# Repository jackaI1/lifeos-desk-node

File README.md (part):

# LifeOS Desk Node

I built a small desk display and room monitor because I wanted to see my next class at a glance and keep temperature and humidity readings in LifeOS.

The display is meant to show my next class or task beside the latest room
reading. LifeOS is my planning system. The device program wakes about every
five minutes, reads the sensor and sends readings over Wi-Fi to a small program
beside LifeOS, where they become daily room-log notes.

I can try the sensor queue and screen on my computer with the outage demo below.
It uses the same code as the device, with pretend readings and uploads. For the
physical display, I use the [parts and wiring](#parts-and-wiring) and
[build and flash](#build-and-flash) steps. I have software checks and a board
design; I still need to bench-test an assembled device, including its screen,
sensor accuracy and power draw.

## Try a sensor outage without a board

I use Guile, a program that runs Scheme, to turn a short scenario into sensor
bytes. A C program then feeds those bytes through the device's existing code.
Install Guile 3 with `brew install guile` on macOS or
`sudo apt-get install guile-3.0` on Ubuntu. With a C compiler and Make installed,
run these commands from the repository root:

```sh
make -C replay
guile --no-auto-compile -L replay/scheme replay/compile.scm < replay/examples/outage.scm > replay/build/outage.wire
replay/build/desk-replay --pbm replay/build/screen.pbm < replay/build/outage.wire
```

The example sends 70 good readings and one damaged reading before a simulated
upload. The result reports 64 uploaded, six dropped and one sensor fault. The
screen image is `replay/build/screen.pbm`, a plain black-and-white image file.
The [replay guide](docs/sensor-replay.md) explains how I change the readings,
repeat a sequence and view the image. These checks run the real sensor decoder,
queue and screen renderer, but the sensor and successful upload are simulated.

## Replay many scenarios at once

I built a parallel mode for the desk-node replay because I run a whole set of
sensor scenarios every time I change the firmware, and replaying them one after
another is slow. The replay now takes several scenario files and runs them on
several threads. A thread is a worker inside one program, so the workers can use
different processor cores at the same time. The program prints one summary line
per file, in the order I gave the files.

```sh
make -C replay
guile --no-auto-compile -L replay/scheme replay/compile.scm < replay/examples/outage.scm > replay/build/outage.wire
replay/build/desk-replay --jobs 4 replay/build/outage.wire replay/build/outage.wire
```

Each line is the same summary the single-file mode prints. `--jobs 1` runs
everything on one thread, and the output is byte-for-byte the same for any number
of threads. The tests run 240 jobs at 2 to 64 threads and compare every byte.
If one file is bad, the program prints the first bad file's name and reason to the
error output, prints nothing else, and exits with an error.

The main thread reads each file into one of eight slots in a block of shared
memory. Workers take the next file in order, replay it, and keep their results in
their own lists. At the end the results are put back in file order and printed.
One mutex, which is a lock, and two condition variables, which let a thread wait
for a signal, keep two threads from touching the same slot at once.

On my Mac, 2000 copies of a 4,095-sample scenario took 0.17 seconds on one thread,
0.08 seconds on two and 0.04 seconds on four. Past four threads, the main thread's
file reading is the likely limit. The parallel mode prints only the summaries. The
screen image (`--pbm`) and UART log (`--uart-log`) still need the single-file
mode, and each file must be under 64 KiB.

CI builds the replay with ThreadSanitizer, which reports threads that touch
shared memory without a lock, and with AddressSanitizer, which reports bad memory
access. Both run in the sensor replay job on Linux and macOS. The locking rules,
the shared memory block and the reasons for each choice are in the
[threading design](docs/parallel-replay.md).

## Check a wire recording without a board

I use sigrok, a tool that reads logic-analyzer recordings, to decode the sensor
messages and serial output. On macOS, install `brew install sigrok-cli guile`;
on Ubuntu, use `sudo apt-get install sigrok-cli guile-3.0 build-essential`.
With Python 3.11 or newer, Make and a C compiler, run from the repository root:

```sh
python3 -m venv .venv
.venv/bin/python -m capture.demo
.venv/bin/python -m capture.decode replay/build/captures/clean.sr
```

The demo generates clean and deliberately damaged recordings from the same sensor
scenarios and serial-log code used by the replay. Each clean recording gives one
25 C / 50% reading and 83 serial bytes with no findings. Each damaged recording
reports a rejected address, a missing acknowledgement clock, a bad sensor checksum,
an unfinished message and a serial framing error, meaning a missing stop bit.
The recordings and readable JSON reports are in `replay/build/captures/`.

For a real recording, run `.venv/bin/python -m capture.decode wake.sr --report report.json`.
The tool accepts sigrok `.sr` sessions and uniformly sampled CSV exports. The
[capture guide](docs/capture-decoding.md) covers recording pins, channel names,
sample rates, changing scenarios and reading fault locations. Generated captures
are synthetic; they do not establish that an assembled board works.

## Try the room-control demo

From the repository root, with Python 3.11 or newer:

```sh
python3 -m venv .venv
.venv/bin/python -m pip install -r automation/requirements.txt
.venv/bin/python -m automation.gateway --demo
```

Leave that running and open another terminal in the same folder:

```sh
.venv/bin/python -m automation.check
```

The check prints the room readings, asks for heat, then lowers the target and
checks that heat and fan turn off. It restores the previous settings when done.
Press Ctrl-C in the first terminal to stop the demo and release its connections.
The outputs are simulated; they do not switch a heater or fan in my room.

Modbus TCP and BACnet/IP are two network protocols, or sets of rules for exchanging
readings and commands. This demo exposes the same readings and thermostat through
both. The [building-control guide](docs/building-automation.md) explains the point
addresses, how to connect the existing desk-node readings, and how these protocols
fit into heating, ventilation, air conditioning and electrical systems.

## Check noisy room readings

I use a moving median, the middle reading in a small sliding group, to remove
isolated spikes. A low-pass filter then keeps slow changes and reduces faster
ones. An FFT, a calculation that separates repeating changes by frequency, helps
me find interference that repeats at a regular interval.

The demo above makes a week's worth of five-minute readings with a known room
temperature, a faster unwanted cycle, random noise and occasional spikes. With
the default seed, the typical error falls from 0.5232 C to 0.1109 C after
filtering. The [short comparison report](docs/signal-analysis-report.md) includes
the raw and filtered errors and the detected noise frequencies. These are
software results against a simulator, not measurements of the physical sensor.

For a real adapter database, I choose one device and analyze a continuous stretch
of readings. The database opens read-only; the report goes into a new folder:

```sh
.venv/bin/python -m analysis --database room.sqlite3 --device desk-1 \
  --channel temperature --cutoff-hz 0.000277777778 --output analysis/build/room
```

This example keeps changes slower than roughly an hour and removes faster ones.
The [guide](docs/signal-analysis.md) covers choosing that boundary, humidity and
CSV input, missing readings, the estimated noise ratio and the filter's limits.
The filters run after collection; they do not change live readings or thermostat
commands. Five-minute logs cannot identify rapid electrical noise such as mains
hum, and smoothing can remove a real rapid change too.

## Rehearse a controller or connection fault

I can check the sensor's Bluetooth packet, Wi-Fi retry decisions and damaged
GPS or vehicle-data recordings on my computer. I can also run the C++ sensor
program on an emulated STM32 and follow a deliberately triggered processor
fault back to its instruction. The [embedded guide](docs/embedded-lab.md)
explains the commands, what each check means and what is simulated.

For a longer control experiment, my [controller rehearsal](robot_controller/)
records timing and sensor data while a simulated heater and two-joint arm run.
Its saved readings feed the same controller-message decoder above. The
[connection rehearsal](network_lab/) tries two delayed or interrupted upload
links and a radio waveform with a simulated frequency shift. Both run without
physical machinery or a paid cloud account.

I also keep a [water-probe board](hardware/leak/) and a
[light-input circuit calculation](hardware/simulation/report.md) here while I
learn how to extend the node. They include circuit checks and simulation plots;
neither circuit has been manufactured. The [Linux sensor experiment](linux_sensor/)
puts the same checked sensor bytes behind a device file inside an emulated ARM
computer. The [concurrent receiver](tcp_telemetry/) and
[port-switch service](optical_switch/) are separate local networking experiments.

## Plan the board and connections

I can compare the original USB board with a smaller battery design before
ordering either one. From this folder, with Python 3.11 or newer, run:

```sh
python3 -m power_budget.compare
```

It shows where current goes and estimates battery life. With the documented
example assumptions, calculated average input current falls from 11.960 mA to
6.715 mA. These are datasheet calculations, not measurements. The new
[48 × 54 mm battery board](hardware/revb/README.md) has a charger and a regulator
that uses less current itself. I still need to build it and fill in the
[bench measurement sheet](docs/power-and-battery.md#bench-sheet-intentionally-empty).
I also have an [antenna matching calculator](docs/antenna-matching.md) that reads
radio measurements and suggests small components to reduce reflections. Its
included example uses clearly labelled synthetic data; I have not measured an antenna.

I use a wiring plan for removable sensor and programming leads so I can cut
and label each wire and check it before powering the board. With Python 3.11 or
newer, I can make the documents without a board or extra packages:

```sh
python3 -m harness.check harness/example.json
python3 -m harness.generate harness/example.json --output harness/build
```

Open `harness/build/harness.svg` for the drawing and the CSV files for the cut
list, labels and continuity and polarity test sheet. The example covers the J2
sensor expansion and J3 programming header. The [harness guide](docs/harness.md)
explains how to change lengths and pin assignments and check the real wiring.

I also keep a purchasing record for the board so I can check replacements and
missing material declarations before ordering parts. It covers all 31 components,
with nine replacement candidates and a spreadsheet for an assembler. With
Python 3.11+, KiCad 8 and its command-line tools installed, I can try it without
a board or an account:

```sh
python3 -m venv .venv
.venv/bin/python -m pip install -r hardware/components/requirements.txt
.venv/bin/python -m hardware.components --boards 10
```

Open `hardware/build/components/desk-node-cm.xlsx`, or download the
[example spreadsheet](hardware/components/review/desk-node-cm.xlsx). The
[parts guide](docs/components.md) shows how I load the same records into InvenTree,
a free parts manager, and explains the risk report. RoHS and REACH are rules about
restricted substances; missing manufacturer evidence stays marked unverified.
The replacement parts are candidates that still need board testing.

I can also check whether sudden jumps in the room log are likely to be noise.
The analysis tool smooths isolated spikes and faster variations, then shows which
repeating changes remain. To try it without a board, with Python 3.11 or newer,
run from this folder:

```sh
python3 -m venv .venv
.venv/bin/python -m pip install -r analysis/requirements.txt
.venv/bin/python -m analysis.demo
```

Open `analysis/build/demo/report.md` for the comparison against known true
readings. The [analysis guide](docs/signal-analysis.md) shows how I use the same
filters on my saved room logs. All demo readings are generated on the computer.

I can also rehearse damaged controller messages before connecting a controller.
The recording tool turns bytes into temperatures and heater/fan commands, reports
missing or damaged messages and turns simulated outputs off when a check fails.
CAN is a wired message network; its FD variant carries longer messages. To try it:

```sh
python3 -m venv .venv
.venv/bin/pip install -r can_monitor/requirements.txt
.venv/bin/python -m can_monitor.replay --generate /tmp/desk-can.jsonl --faults
.venv/bin/python -m can_monitor.replay /tmp/desk-can.jsonl --tail 3
```

The [controller recording guide](docs/can-control.md) explains the errors,
message rates and Linux virtual network. These are simulated messages, including
a 64-byte CAN FD snapshot. My current desk board has no CAN transceiver.

For missing room logs, I can separately test delayed or lost network replies and
save sensor batches through an encrypted message broker. The
[connection guide](docs/network-monitoring.md) gives the demo commands, network
layout and alarm rules. The [charging model](power_budget/charging.py) adds a
calculated charge-time estimate to the existing battery budget.

## Parts and wiring

The controller is an ESP32-WROOM-32E, a small computer with Wi-Fi and 4 MB of
program storage. I use an OLED, a compact light-emitting screen, for the display.
SPI and I²C are the wired connections to the screen and sensor; UART is the
serial connection used to load the program and read logs. The firmware needs:

- An SHT31 temperature/humidity sensor at address `0x44`.
- An SSD1306 128 by 64 OLED module with a seven-pin, four-wire SPI connection.
- A regulated 3.3 V supply for the controller and peripherals, from USB desk power.
- A 3.3 V USB-to-UART adapter for flashing and reading the serial log.

The [wiring guide](docs/pinout.md) gives the exact pins, power requirements and
pull-up resistors. A four-pin I²C OLED is a different variant; select the legacy
display option explicitly if using that wiring. Do not connect both displays.
The OLED stays powered while the ESP32 sleeps. Rev A uses USB desk power;
Rev B adds a battery option while retaining that display behavior. Neither has
a measured battery-life claim.

## Circuit board

I designed the [board](hardware/) to hold the controller, temperature and humidity
sensor, and USB-C power supply. The screen plugs into it. A separate USB-to-UART
adapter loads the firmware and lets me read its logs. The
[board guide](hardware/README.md) explains the connections, parts and files needed to order or build one. This version has not been manufactured yet.

## Check the power-up on a bench

I built a bench check because I need the same power-up measurements every time I change the board, and I want them written down. The script drives a programmable power supply and an oscilloscope. It sets the 5 V input, turns it on, and records the ripple on the 3.3 V regulator's output (the small repeating wiggle on a supply line) and how long after the 5 V input that output comes up. It also reads how much current the board draws. Each result is compared with a limit in a text file, and each run is saved in a folder named with the time it ran.

I don't have the lab instruments here, so the check runs against simulated ones. It sends SCPI, the standard text commands most bench supplies and scopes use, through PyVISA, a Python library that talks to instruments. A second library, pyvisa-sim, answers those commands from a file that describes a simple board. To run it:

```sh
python3 -m venv .venv
.venv/bin/python -m pip install -r bench/requirements.txt
.venv/bin/python -m bench
.venv/bin/python -m bench --inject ripple
```

The first run passes all five checks: 8 mVpp of ripple (limit 30), a 1.5 ms delay for the regulator (limit 0.2 to 10 ms) and 60 mA of input current (limit 150 mA). The `--inject` option adds a fault to the simulated board. `ripple` adds 60 mVpp, and `late-rail` starts the regulator 14 ms late. Each fault fails the check it targets and nothing else, and the tests check that. Each run writes a CSV of measurements, a CSV of the captured waveforms and a short report into `bench/build/runs/`. The limits in `bench/limits.toml` are bring-up targets I picked, not datasheet numbers. The [bench guide](docs/bench-automation.md) covers the commands, how the simulator models the board and how to point the script at real instruments.

## Export the light-input circuit for OrCAD

I built an OrCAD export because I wanted to learn Cadence OrCAD, a circuit
design and simulation program that many electronics teams use. My light-input
circuit is in KiCad, so I wrote a script that turns it into an OrCAD PSpice
netlist. A netlist is a plain text file that lists each part and the points it
connects to. The script takes the feedback resistor and capacitor values from the
KiCad drawing, so the netlist cannot drift from the drawing. It also refuses to
write a netlist if those two parts are not wired to the amplifier's output and
input pins.

To check the file, the script runs it in ngspice, a free simulator that runs on
my Mac. It runs DC, frequency and time-step analyses from the same file and
compares the results with my hand calculations.

```sh
python3 -m hardware.simulation.orcad --out hardware/simulation/build/orcad
```

This needs `kicad-cli` and `ngspice` installed. It writes `light-front-end.cir`,
the OrCAD netlist, and `check.json`, the measured results. On my last local run
the gain was 99,999 ohms, the bandwidth was 16.8 kHz against a hand value of
15.9 kHz, and the step settled at 1.74998 V. The [circuit report](hardware/simulation/report.md)
explains what the model leaves out. OrCAD is a desktop program, and I have not
opened this netlist in it yet, so the checks I have are the ngspice run and the
tests in `hardware/simulation/tests/test_orcad.py`.

Syntax note: the two behavioral sources (the supply reference and the output
clamp) are written as PSpice `VALUE {...}` cards, not the `V=` form that ngspice
accepts on its own. PSpice does not read `V=`, so I changed them. The tests check
the card shapes, but no PSpice program has read the file yet, so importing it into
OrCAD is still the next step.

## Build and flash

Install [ESP-IDF v5.4.2](https://docs.espressif.com/projects/esp-idf/en/v5.4.2/esp32/get-started/index.html)
with its ESP32 toolchain, the tools for building and loading the device program.
In an activated ESP-IDF shell, from this checkout:

```sh
cd firmware
idf.py set-target esp32
idf.py menuconfig
idf.py build
idf.py -p /dev/cu.YOUR_USB_UART flash monitor
```

In menuconfig, open LifeOS Desk Node and choose the display, Wi-Fi settings,
service address and device token. Replace the example serial port with the adapter's
port. The [firmware guide](firmware/README.md#build-and-flash) covers programming
mode, serial logging and configuration. Configured binaries contain the Wi-Fi
credentials and token; keep them and `sdkconfig` private.

## Connecting it to LifeOS

The ESP32 talks to the included [API adapter](firmware/tools/desk_api.py), a
small service that translates requests between the device and LifeOS. An API
is the set of requests programs use to communicate. The adapter needs Python
3.9 or newer and stores readings in SQLite, a database kept in a local file.
Follow the
[adapter setup](firmware/README.md#lifeos-api-adapter) to create a private device
token, try the isolated demo and then configure a real LifeOS connection.

Demo mode uses fictional events and never contacts LifeOS. Its default address,
`127.0.0.1:8091`, is for trying it on the computer. For the desk device, use a
network-reachable address and the HTTPS setup in the guide. HTTPS encrypts
the connection and checks the server's identity. Keep LifeOS account
credentials on the computer, not on the microcontroller.

The adapter picks the earliest upcoming school event or task deadline visible
through LifeOS. A date-only deadline says that its time is unknown. Readings go
into new daily notes named `Desk room <day> <device>`. Retries do not duplicate
readings, and edits to a managed note's text stop syncing rather than overwrite
the edit.

## When the connection is down

The screen keeps the last fetched event and marks it offline, so it can be stale.
Up to 64 readings wait for upload across sleep cycles. If that fills, the oldest
reading is dropped and the screen shows a loss count. Turning the power off loses
those pending readings; they are not saved to flash. Invalid sensor readings
are not turned into made-up values.

## Read the room sensor from my phone

I added Bluetooth Low Energy to the desk node because I wanted to read the room temperature and humidity from my phone without needing Wi-Fi. Bluetooth Low Energy is a short-range radio that uses very little power. The desk node now advertises as `Desk room sensor`, so my phone can find it, connect and read the latest values. The default build leaves Bluetooth out, so existing builds work as before.

After each wake, the node takes its usual reading, uploads it over Wi-Fi as before, and then keeps Bluetooth on for a short window, 30 seconds by default. While a phone is connected, the node reads the sensor again every 10 seconds. It sends a notification only when the temperature has moved by 0.1 °C or the humidity by 0.5 %, and never more than one every 10 seconds. When the window ends, the radio shuts off until the next wake.

The values use the standard Environmental Sensing service from the Bluetooth standards group, so any generic Bluetooth app can read them. The firmware uses NimBLE, the small Bluetooth stack that ships with ESP-IDF, the official ESP32 software kit. Temperature is a signed 16-bit number in hundredths of a degree (characteristic `0x2A6E`). Humidity is an unsigned 16-bit number in hundredths of a percent (`0x2A6F`). The encoding and the notification rule are plain C in [`firmware/components/desk_ess`](firmware/components/desk_ess/). The host tests in [`firmware/tests/test_ess.c`](firmware/tests/test_ess.c) run them under AddressSanitizer and UBSan, with out-of-range values and bad checksums included: 37 checks.

How to try it:

1. Build the Bluetooth version with `idf.py -D SDKCONFIG_DEFAULTS="sdkconfig.defaults;sdkconfig.ble.defaults" set-target esp32`, then `idf.py build` and flash it.
2. On a phone, open nRF Connect (a free Bluetooth scanner app), scan, and tap `Desk room sensor` within 30 seconds of a wake. The node wakes every 5 minutes by default.
3. Read the temperature characteristic (`0x2A6E`). It shows two bytes such as `59 08`. Decode them with `python3 firmware/tools/ess_decode.py temperature "59 08"`, which prints `21.37 degC`.

The phone only sees the node during the window after each wake. It is not a live stream. A shorter sleep interval gives more windows but uses more power. I have not run this on a real board yet. CI builds the Bluetooth version next to the default one, and runs the encoder tests on every push. The [firmware README](firmware/README.md#bluetooth-low-energy-optional-build) has the build details.

## Send readings over a wired CAN link

I built a wired CAN link for the desk node because Wi-Fi drops, and when it does I lose the room readings until it comes back. CAN is a wired message bus: devices share two wires, and each short message reaches every device on the bus. The node sends its latest temperature, humidity and fault flags once per wake cycle, using the ESP32's built-in CAN controller. A second device on the bus, or my laptop with a recording, can read them later.

The analyzer reads a recorded CAN log and flags what I care about: a gap in the heartbeat (the regular message that shows the node is alive), values outside the range the message layout allows, the node's own sensor and queue fault flags, and bus-off, when the controller stops sending because too many of its messages failed. It runs on a computer with no board attached:

```sh
python3 -m venv .venv
.venv/bin/python -m pip install -r can_monitor/requirements.txt
.venv/bin/python -m can_monitor.analyze can_monitor/examples/candump/desk_node_clean.log
.venv/bin/python -m can_monitor.analyze can_monitor/examples/candump/desk_node_faults.log
```

The clean log passes. The second file is the same log with damage I added on purpose: 10 readings missing, a humidity of 105 %, a sensor fault, a bus-off event, a damaged line and a time that goes backwards. The analyzer reports each one and exits with status 1. Both logs come from a simulated node on a virtual bus, not from a real board. The [CAN guide](docs/can-log-analysis.md) lists every finding, the byte layout and the firmware switch (`CONFIG_DESK_CAN_ENABLE`). The desk board has no CAN transceiver yet, so the link has not run on a real bus. CI builds the firmware with the CAN link enabled, runs the C encoder tests, and checks the same bytes against the message file in Python.

## Check the case before printing

I built a set of simulations for the case because I wanted to know whether it fits the board and survives being knocked before I print it. The scripts in [mechanical/](mechanical/README.md) draw the case from its dimensions, load it on a computer the way a lid screw or a drop would, and report the peak stress, how far it bends and its safety factor against yielding. A second script adds up the size errors of the board, the standoffs and the printed case to check the screw fit.

The first run found one thing to change: with the 3.2 mm mounting holes on my board, an M3 screw misses the worst-case fit by 0.115 mm, and a 3.5 mm hole passes. The numbers are in [mechanical/docs/study.md](mechanical/docs/study.md), and the setup steps are in the [mechanical README](mechanical/README.md). The checks run in GitHub Actions on every change to that folder.

## Check my room readings for odd values

I built a small anomaly check for the temperature and humidity readings because I want the desk node to notice a sensor spike or a stuck value itself, before it reaches my room log. A small neural network learns what a normal reading looks like from a log, and a window of four readings gets a high score when it looks wrong. I shrank the model to eight-bit integers, so it could run on the ESP32 later. The C code uses only integer arithmetic.

On a simulated log with known faults, the eight-bit model gets the same accuracy as the full-precision model (0.968 on the held-out part), agrees with it on 99.56 % of windows, and uses 223 bytes for its weights instead of 592. It catches spikes, humidity jumps and dropouts every time. It misses stuck readings, because four identical values look like a calm room. The [anomaly README](anomaly_int8/README.md) has the numbers and the per-layer scales, and [anomaly_int8/docs/results.md](anomaly_int8/docs/results.md) has the full report. To run it:

```sh
cd anomaly_int8 && python3 -m venv .venv && . .venv/bin/activate
python -m pip install --index-url https://download.pytorch.org/whl/cpu torch==2.9.1 && python -m pip install -r requirements.txt
python -m pytest && python -m anomaly_int8 run
```

## Check the sensor checksum in hardware

The sensor sends a checksum with each reading, and the firmware throws away readings whose checksum does not match. I wrote the same check as logic blocks in Verilog, the language that describes chips and FPGAs, because a hardware version is one option for the sensor path later. The blocks are tested in simulation against the same scenario files the firmware tests use, including the ones with deliberately corrupted checksums. The [rtl README](rtl/README.md) explains each block.

The word checker agrees with the replay tool on all 2,204 words I tested, and the reading buffer's built-in self-test finds all 512 memory stuck-at faults I injected, and all 22 scan-chain faults. The sensor path also maps onto 588 LUT4 cells and 440 flip-flops in Yosys for an iCE40 FPGA.

```sh
cd rtl && python3 -m venv .venv && . .venv/bin/activate && python -m pip install -r requirements.txt
make test PY=python3     # lint, cocotb frame tests, Verilator benches, cross-checks
make synth               # FPGA-style synthesis and logic depth
```

## Place and route the sensor block

I ran the sensor block through OpenROAD, an open-source chip design flow, to check that it can run at the speeds I would need for a chip or an FPGA version of the sensor path. The flow does synthesis, placement and routing on the open Nangate45 cell library. I swept the clock period and the core utilization and recorded the timing slack, area and power for each run. Every run meets timing, the tightest at 1.2 ns with 0.080 ns to spare, and CI fails if the chosen 1.2 ns constraint ever stops closing. The table and the commands are in [rtl/README.md](rtl/README.md) and [rtl/docs/openroad-sweep.md](rtl/docs/openroad-sweep.md).

## Run the sensor check on an FPGA board

I wanted the sensor checksum logic to run on a real FPGA, a chip you can reprogram, and not only in a simulator. The sensor check in `rtl/` is written in Verilog, so I added a board version of it for the iCEBreaker, a small board with an iCE40 UltraPlus FPGA, a 12 MHz clock and a USB serial port. Its FPGA is one of the open-source chip families, so I can build the program for it with free tools.

The computer sends sensor bytes over the USB serial port. Each transfer starts with a length byte, then the bytes. The board checks each six-byte frame in the same hardware block as before, keeps the good ones and sends back six bytes with the good, bad and cut-short counts. The green LED is on while a transfer is arriving. The red LED comes on after any bad or cut-short frame.

```sh
cd rtl && python3 -m venv .venv && . .venv/bin/activate && python -m pip install pyserial
python3 board/icebreaker/host.py --port /dev/tty.usbserial-XXXX --demo
```

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
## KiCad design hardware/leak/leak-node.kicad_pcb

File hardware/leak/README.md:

# A water-probe board for my desk node

I built a small water-probe interface because I wanted to learn how to add a
simple leak indication beside the desk node's room readings. Two external probe
contacts act like a resistance: water lowers it, the board turns on a red light
and its output changes for a microcontroller to read. This is an unmanufactured
prototype, not a dependable flood alarm.

`leak-node.kicad_sch` is the circuit drawing and `leak-node.kicad_pcb` is its
45 by 35 mm, two-copper-layer layout. The exact footprints are kept in `Leak.pretty` and embedded in the board;
`bom.csv` records values, footprints and manufacturer part numbers. The MCU header is J1:
1=3.3 V, 2=ground, 3=active-low alert, 4=probe voltage for an ADC. J2 connects
the two external conductive probe contacts. The board does not include an MCU.

With KiCad 8 command-line tools installed, from the repository root:

```sh
hardware/leak/check.sh
```

I get electrical-rule and layout-rule reports, a PDF circuit drawing, a bill of
materials with manufacturer part numbers, and Gerber/drill files for fabrication
in `hardware/leak/build`. CI fails for any reported rule violation, including
schematic/layout disagreement, and saves those files as downloadable artifacts.
The check does not open a desktop application. Source changes can be regenerated
with `scripts/generate.py`; `scripts/board.py` does headless placement and imports
batch routes. The committed board is already routed and needs no router to check.

## Why these parts and dimensions

A 1 megohm pull-up keeps dry-probe current low. An LMV331 comparator compares the
probe voltage with half the supply from two 100 kilohm resistors. Its output
sinks current for the LED and has a separate 10 kilohm pull-up for the MCU. A
10 megohm feedback resistor gives hysteresis, so the output does not keep
switching at exactly one resistance. The ideal wet threshold is about 909
kilohms and release threshold about 1.11 megohms; real leakage, comparator offset,
probe contamination and water composition can move them. I must measure this
before choosing a useful physical threshold.

The 100 nF capacitor is beside the comparator supply. I use 0.25 mm signal
tracks, 0.20 mm net clearance, 0.6 mm vias with 0.3 mm drills and at least
0.3 mm copper-to-edge clearance. The current is low, so these widths are chosen
for routing and fabrication margin, not a high-current power path. The high
resistance input makes clean PCB surfaces, short probe leads and protection
against electrostatic discharge important. Continuous DC can corrode a wet
probe; intermittent power and a corrosion study are future hardware work.
The [simulation report](../simulation/report.md) shows the ideal threshold sweep
and the separate light-sensor amplifier calculation. No actual leakage, battery
draw or water response has been measured.

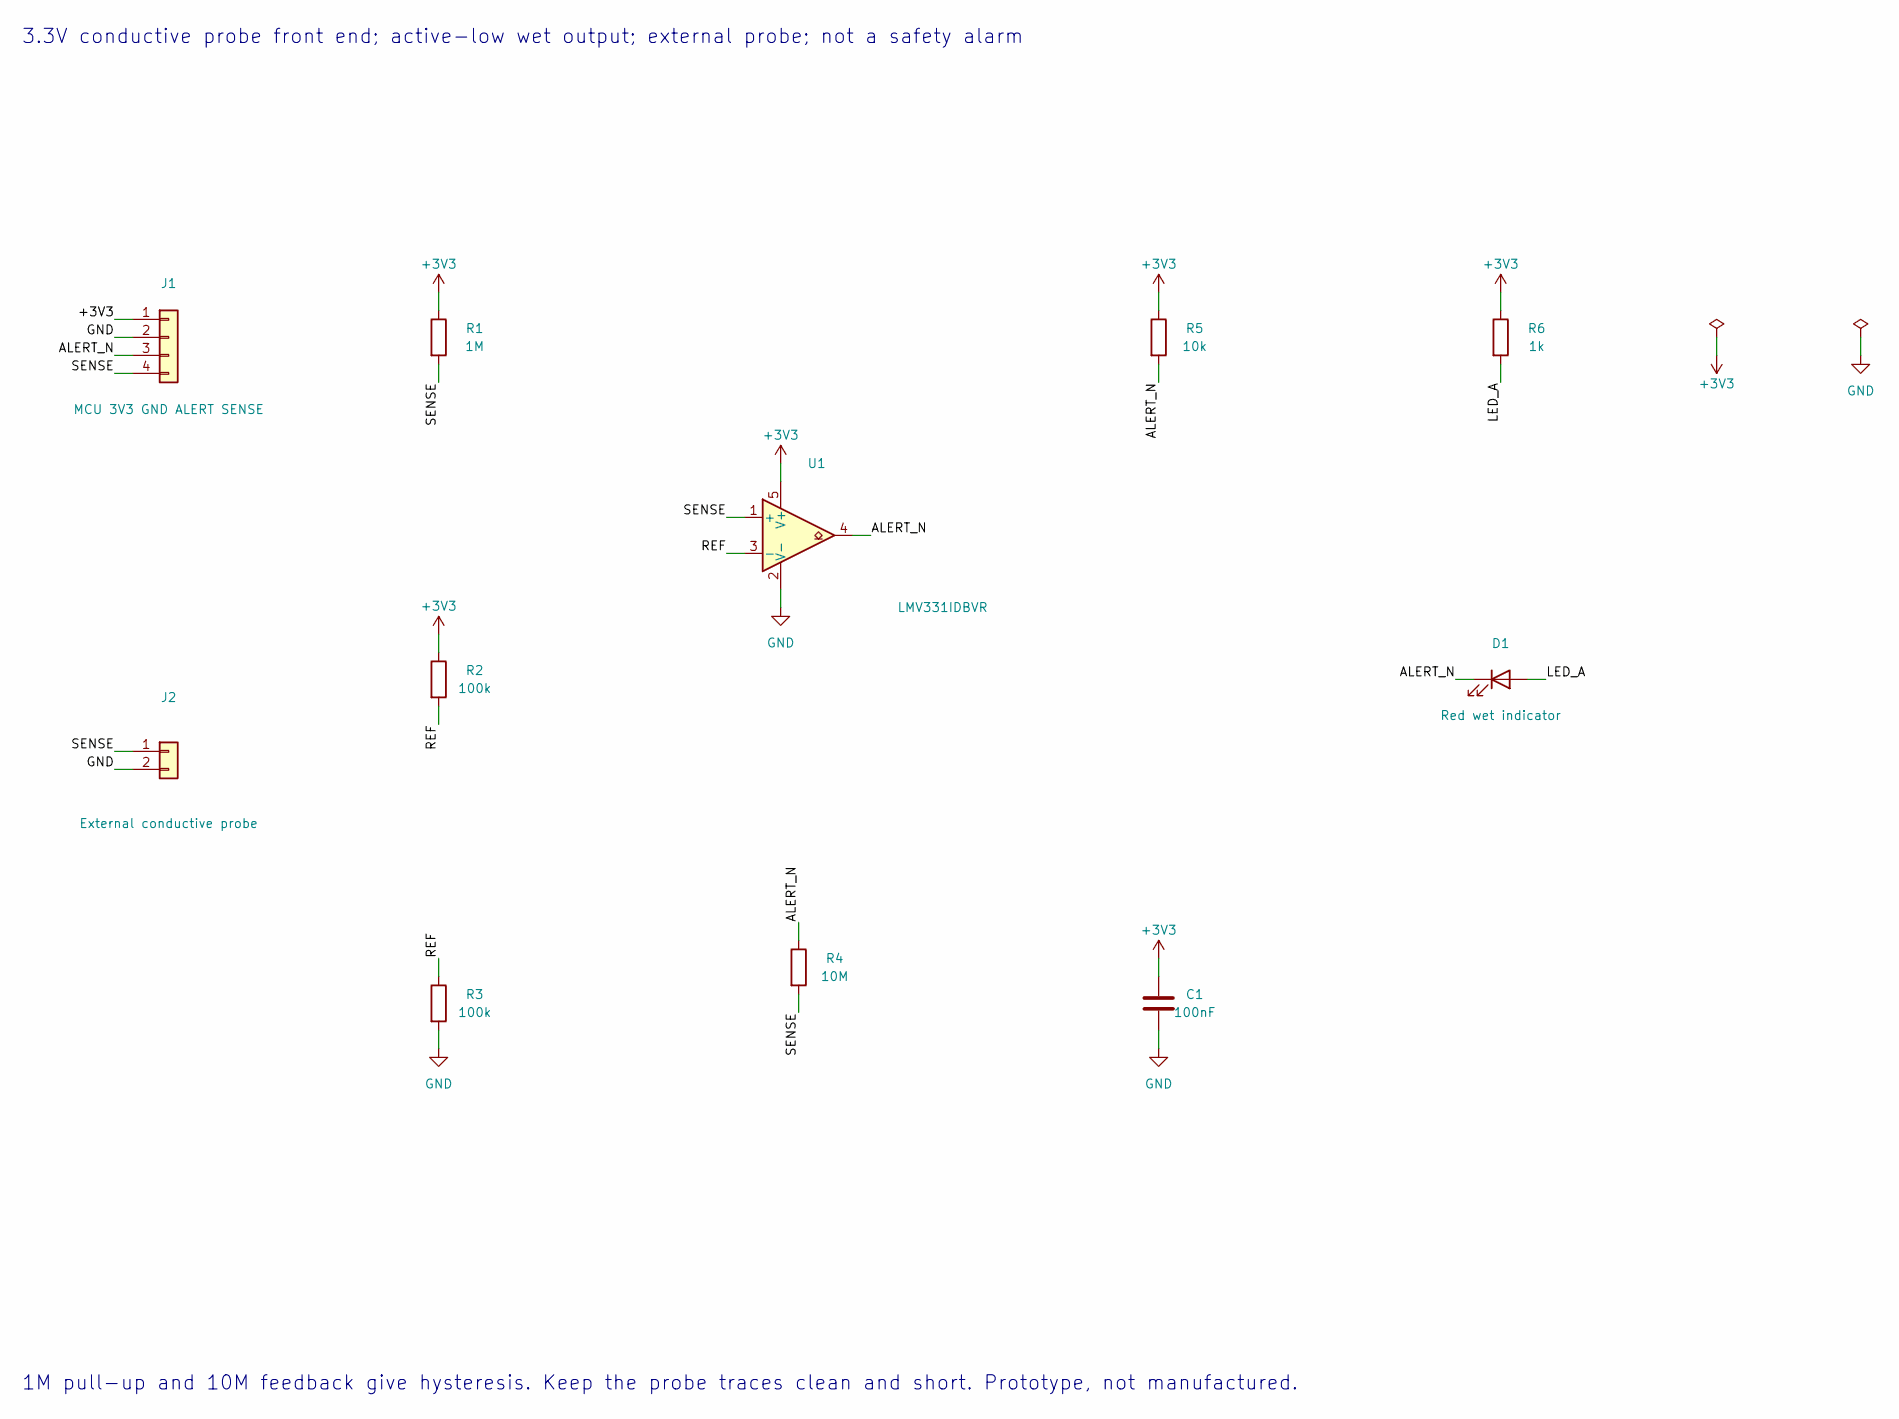
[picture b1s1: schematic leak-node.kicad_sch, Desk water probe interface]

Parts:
C1: 100nF; C_0603_1608Metric; MPN GRM188R71C104KA01D
D1: Red wet indicator; LED_0603_1608Metric; MPN LTST-C190KRKT
J1: MCU 3V3 GND ALERT SENSE; PinHeader_1x04_P2.54mm_Vertical; MPN Samtec TSW-104-07-G-S
J2: External conductive probe; PinHeader_1x02_P2.54mm_Vertical; MPN Samtec TSW-102-07-G-S
R1: 1M; R_0603_1608Metric; MPN RC0603FR-071ML
R2, R3: 100k; R_0603_1608Metric; MPN RC0603FR-07100KL
R4: 10M; R_0603_1608Metric; MPN RC0603FR-0710ML
R5: 10k; R_0603_1608Metric; MPN RC0603FR-0710KL
R6: 1k; R_0603_1608Metric; MPN RC0603FR-071KL
U1: LMV331IDBVR; SOT-23-5; MPN LMV331IDBVR

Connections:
+3V3: C1.1, J1.1, R1.1, R2.1, R5.1, R6.1, U1.5 (V+)
/ALERT_N: D1.1 (K), J1.3, R4.1, R5.2, U1.4
/LED_A: D1.2 (A), R6.2
/REF: R2.2, R3.1, U1.3 (-)
/SENSE: J1.4, J2.1, R1.2, R4.2, U1.1 (+)
GND: C1.2, J1.2, J2.2, R3.2, U1.2 (V-)

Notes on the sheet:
3.3V conductive probe front end; active-low wet output; external probe; not a safety alarm
1M pull-up and 10M feedback give hysteresis. Keep the probe traces clean and short. Prototype, not manufactured.

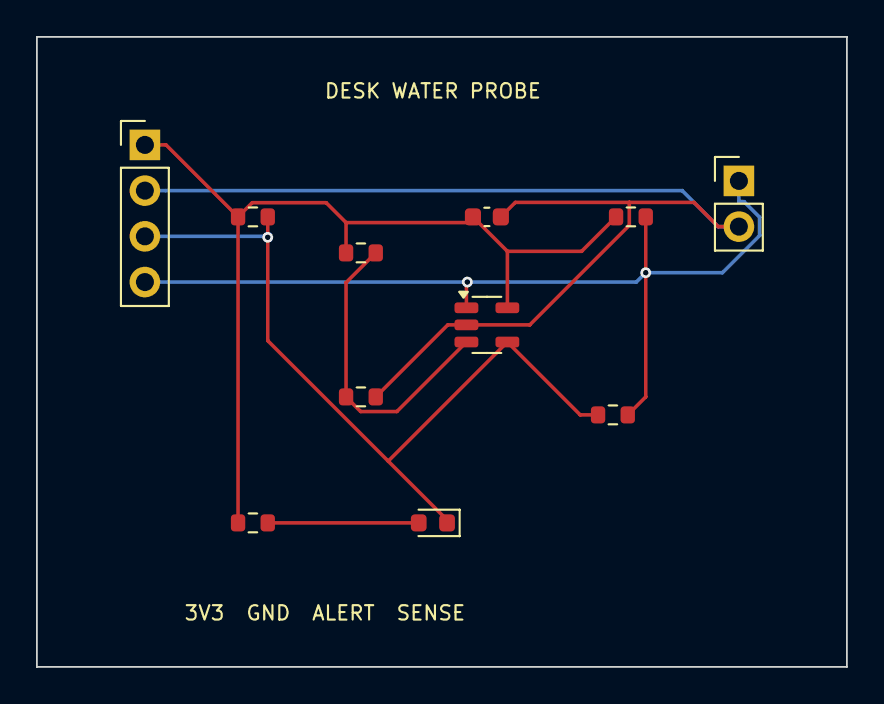
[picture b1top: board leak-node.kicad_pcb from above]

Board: 2 copper layers, 45.0 x 35.0 mm, 11 parts (0 on the bottom side), 6 nets.

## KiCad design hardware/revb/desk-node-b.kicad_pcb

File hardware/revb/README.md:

# Battery desk node, Rev B

I built a smaller battery board because the USB version's regulator and power
light keep drawing current between updates. This version keeps the working
firmware pin assignments and the screen's last image, adds a LiPo charger, and
uses a regulator with a much smaller standing current. It is a routed prototype
design, not an assembled or measured board.

Open [desk-node-b.kicad_pro](desk-node-b.kicad_pro) in KiCad 8 to inspect the
circuit drawing and physical board. With KiCad 8 and Python 3.11 or newer on PATH:

```sh
hardware/revb/check.sh
python3 -m power_budget.compare
```

The first command checks the circuit and copper, checks the firmware pins and
battery connections independently, then exports files into `hardware/revb/fab/`.
The second prints calculated current and runtime. The
[power guide](../../docs/power-and-battery.md) explains every input and has an
empty table for real microamp-meter measurements.

## What changed

| Design choice | Rev A | Rev B |
| --- | --- | --- |
| Board bounding size | 50 × 55 mm | 48 × 54 mm, 5.75% less area |
| Supply | 5 V USB | Protected 1S LiPo, 4.2 V full; USB charges only |
| Regulator | AZ1117C-3.3, 4 mA typical own current | AP2112K-3.3, 55 µA typical own current, 600 mA output rating |
| Always-on light | Red LED through 1 kΩ | Removed |
| Charger | None | MCP73831T-2ACI/OT, 4.2 V, 100 mA set by 10 kΩ |
| Display | Powered throughout sleep | Same, no firmware changes |
| Signal connectors | J2 I²C, J3 UART, J4 SPI | Same pin assignments |

Dimensions describe the **carrier PCB**, not the complete assembled envelope:
the module antenna overhangs the top edge by 6.19 mm and connectors extend beyond
the board. The battery and display are external. The top slot ends at x = 46.5 mm;
the SHT31 sensor remains on the slotted peninsula. Antenna copper exclusions,
0.3 mm minimum drill, two copper layers and 0.15 mm minimum track/space are kept.
The module uses its factory antenna and match; the
[RF calculator](../../docs/antenna-matching.md) is for a future external feed,
not for attaching parts to the carrier's digital pins.

## Battery and charging connections

Use one protected 1S 4.2 V LiPo, nominally 500 mAh or more, with at least a 1 A
pulse rating and a manufacturer-approved charge current of at least 100 mA.
**J5 pin 1 is positive, pin 2 is ground.** Check polarity at the actual plug;
similar JST leads can be wired in opposite directions.

**JP1 must have exactly one two-pin shunt**, rated at least 1 A:

- **Pins 1–2 RUN:** battery feeds SYS and the 3.3 V regulator. The charger's
  battery output is disconnected from the cell.
- **Pins 2–3 CHARGE:** battery feeds the charger. SYS and the entire node load
  are disconnected. The screen goes off and pending readings are lost.

Unplug USB before moving the shunt. Never bridge all three pins. There is no
run-while-charging mode. J1 USB-C retains CC pull-downs, fuse and TVS; it feeds
only the charger. The programming adapter must use 3.3 V logic and leave its
power lead disconnected. J3 pin 2 is a voltage reference, not a power input.

The charger uses 10 µF at USB input and 4.7 µF at BAT. SYS has 10 µF, and the
regulator has 22 µF output plus local ceramic/bulk capacitors. Check ceramic
capacitance after voltage bias. At 100 mA and a 3.0 V cell, charger dissipation
is calculated as `(5 - 3) × 0.1 = 0.2 W`; thermal regulation can reduce current.
STAT is unused, so there is no charge-status light. Charge termination is about
7.5 mA for this exact charger suffix and cannot be confirmed by a light here.

This charger has no cell-temperature input, and this board has no independent
undervoltage cutoff. Use only a protected pack and supervised, room-temperature
charging allowed by its manufacturer. Stop normal operation at **3.7 V loaded**
for the runtime assumption; this is not an automatic cutoff or a guarantee of
regulation. The AP2112's maximum listed dropout at 600 mA is 400 mV, before output
tolerance, cell sag and trace loss. A protected pack's deep-discharge trip is far
below this usable operating point. The regulator may lose 3.3 V regulation first;
measure rail droop under Wi-Fi bursts before relying on stored readings.

## Checks and ordering

`check.sh` fails on every ERC or DRC severity, missing connection or schematic
parity difference, with no ignored violations. ERC checks electrical connections;
DRC checks copper spacing, outlines and connections. It also reproduces the
schematic from `scripts/design.py`, runs the independent fixed pin contract,
and checks the actual PCB outline dimensions. GitHub runs these checks alongside
Rev A's existing fabrication checks and uploads both sets of outputs.

The **committed routed PCB is the layout source**. `scripts/design.py` reuses
Rev A's signal circuit and replaces its supply; the schematic generator embeds
standard KiCad 8 symbols. The layout began with generated placement and
Freerouting 2.1, then received sensor connections and local power/ground repairs.
Regenerate only the schematic with `python3 hardware/revb/scripts/gen_schematic.py`;
edit the PCB in KiCad and rerun checks after layout changes. Do not use Rev A's
board generator on this layout. Library attribution is in
[the hardware library notes](../LIBRARIES.md); the copied WROOM footprint uses
the same 0.3 mm thermal drills and two-layer antenna exclusion.

Before ordering, compare exact manufacturer drawings for the SOT-23-5 regulator
and charger, battery connector polarity and shunt pitch. Review board-edge plug
access, the antenna/enclosure clearance, slots, footprints, paste, thermal vias,
and the fabrication and assembly previews. Supplier identifiers from Rev A's
component database apply to Rev A only; Rev B's exported BOM lists exact new
part numbers but does not claim purchasing approval or complete supplier records.
Neither ERC nor DRC establishes charge safety, heat, battery runtime, RF range,
sensor temperature bias or physical assembly fit.

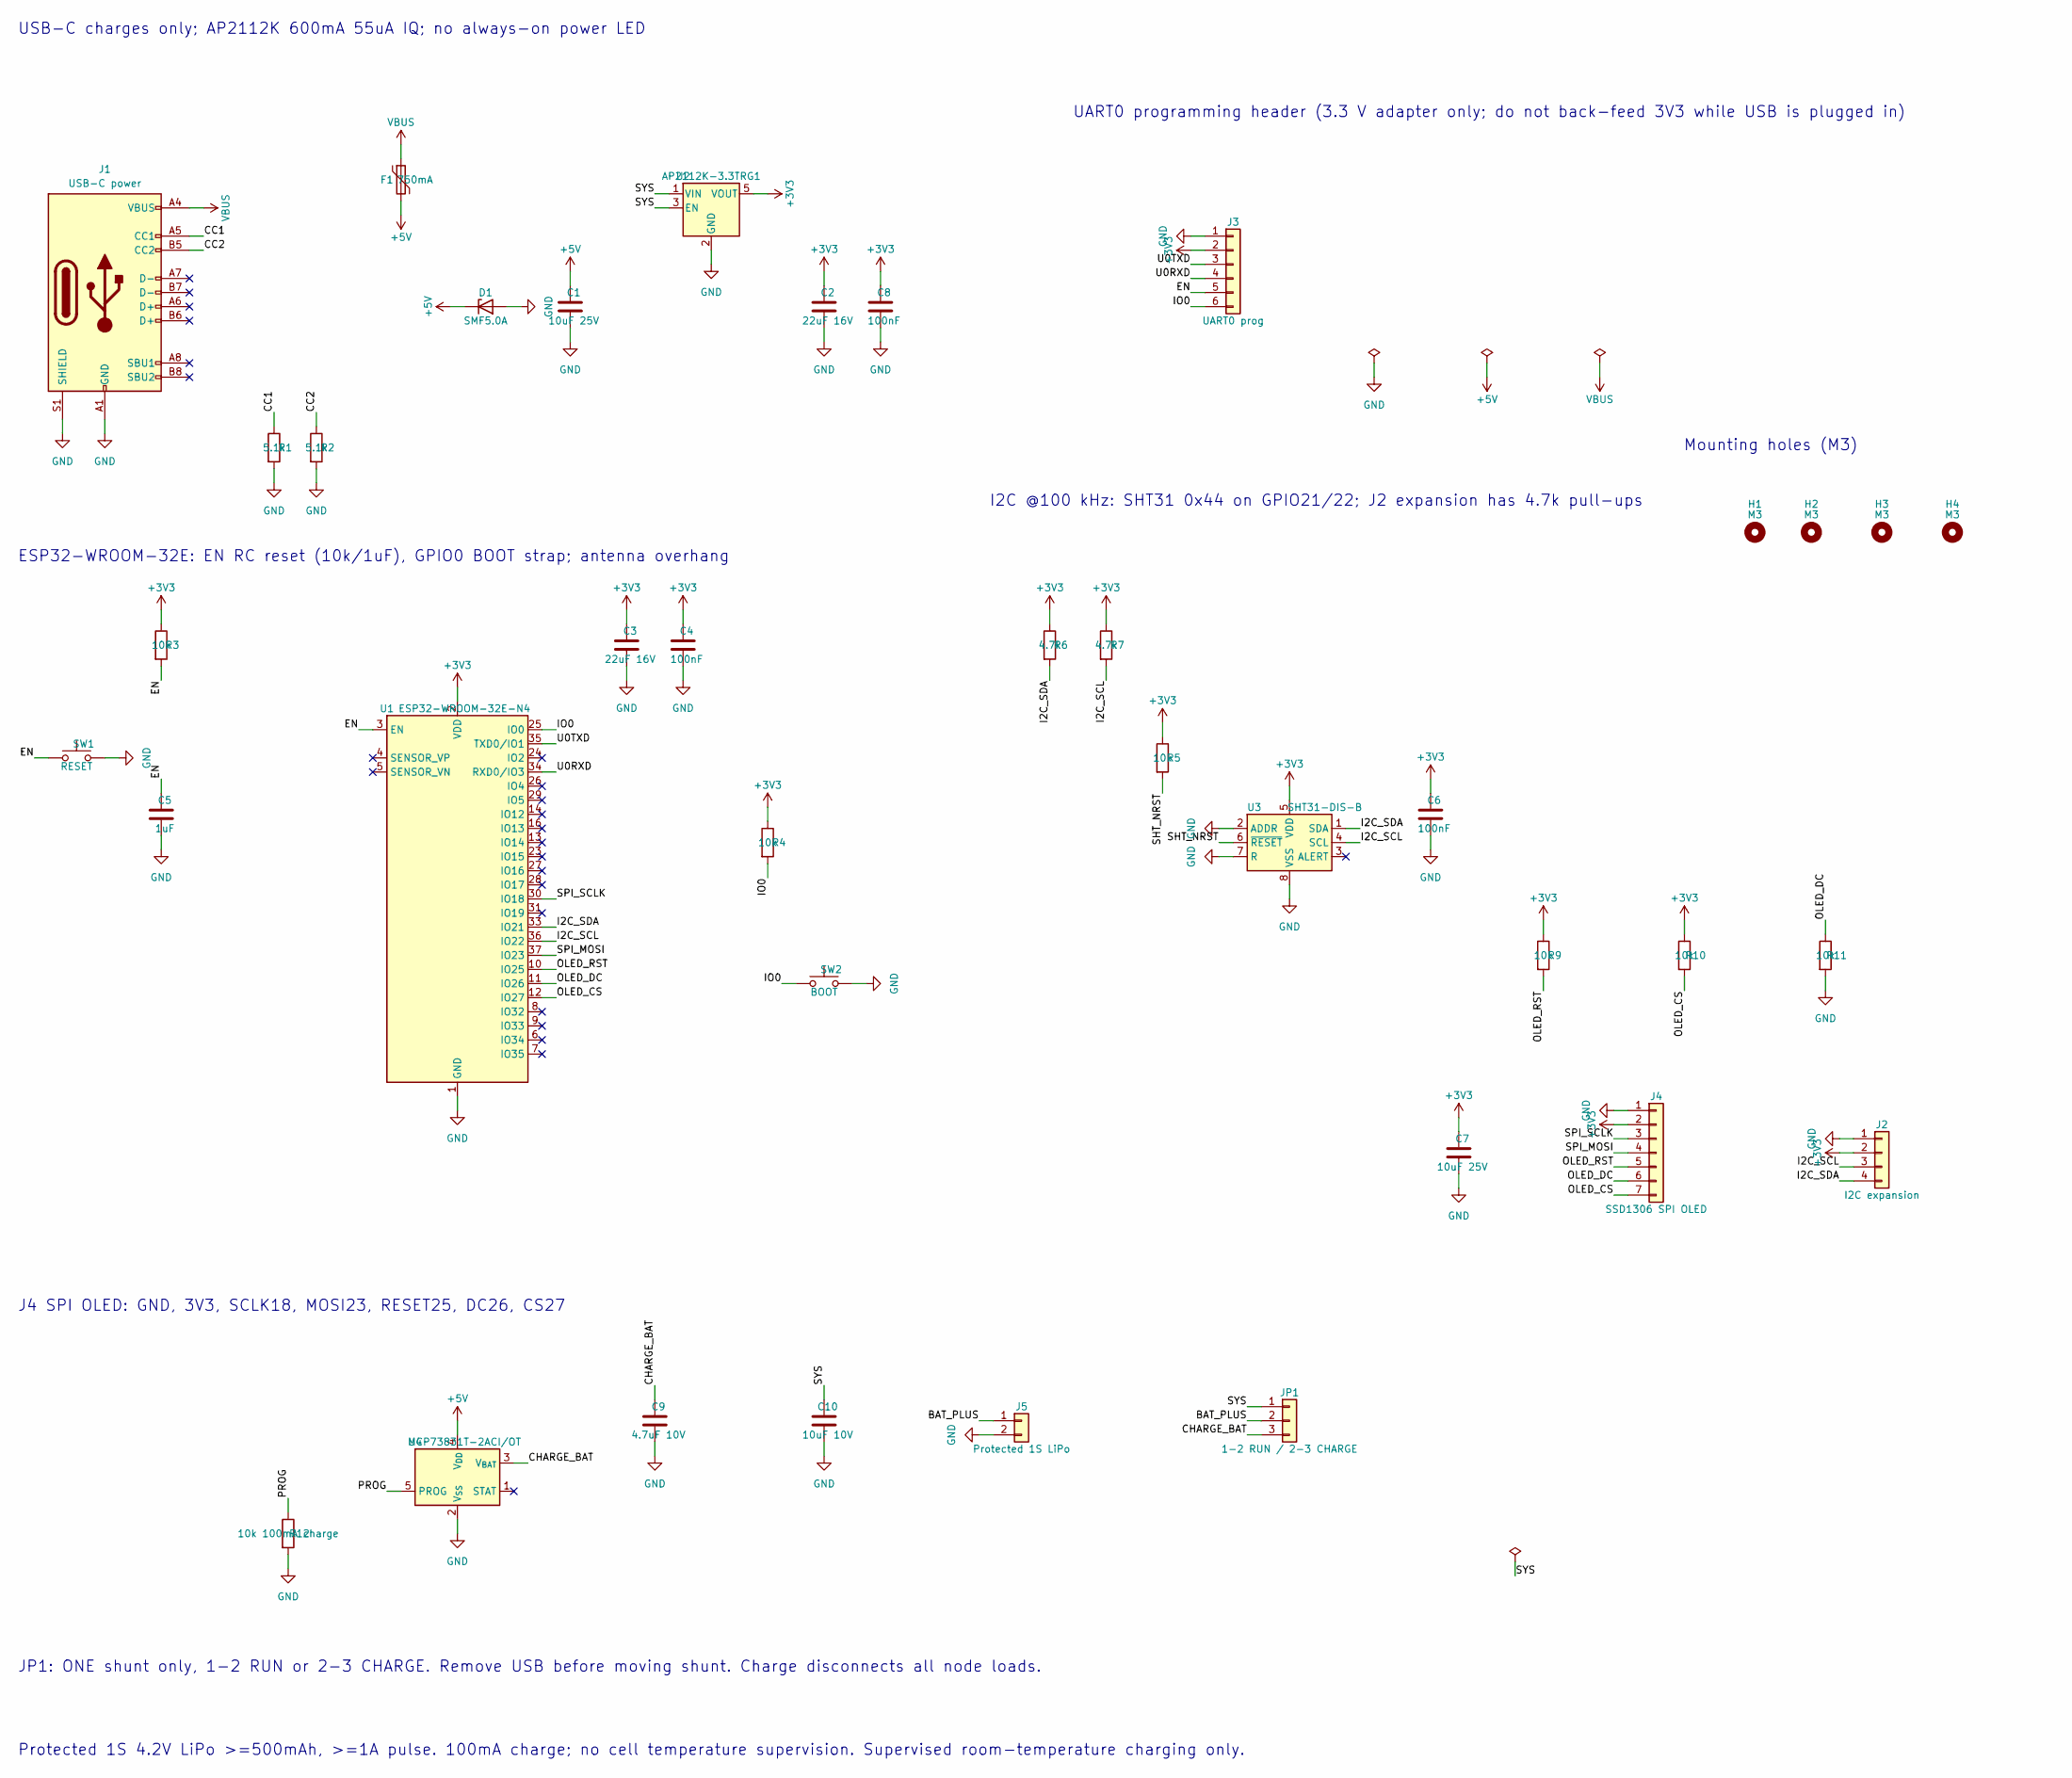
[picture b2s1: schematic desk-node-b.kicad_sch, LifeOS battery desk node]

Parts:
C1, C7: 10uF 25V; C_0805_2012Metric; MPN CL21A106KAYNNNE; LCSC C15850
C2, C3: 22uF 16V; C_0805_2012Metric; MPN CL21A226MOQNNNE; LCSC C98190
C4, C6, C8: 100nF; C_0603_1608Metric; MPN CL10B104KB8NNNC; LCSC C1591
C5: 1uF; C_0603_1608Metric; MPN CL10A105KB8NNNC; LCSC C15849
C9: 4.7uF 10V; C_0805_2012Metric; MPN GRM21BR71A475KA73L
C10: 10uF 10V; C_0805_2012Metric; MPN GRM21BR61A106KE19L
D1: SMF5.0A; D_SOD-123F; MPN MDD SMF5.0A (5 V TVS); LCSC C193402
F1: 750mA; Fuse_1206_3216Metric; MPN Littelfuse 1206L075THYR; LCSC C99563
H1, H2, H3, H4: M3; MountingHole_3.2mm_M3
J1: USB-C power; USB_C_Receptacle_HRO_TYPE-C-31-M-12; MPN HRO TYPE-C-31-M-12; LCSC C165948
J2: I2C expansion; PinHeader_1x04_P2.54mm_Vertical; MPN XFCN PZ254V-11-04P; LCSC C492403
J3: UART0 prog; PinHeader_1x06_P2.54mm_Vertical; MPN XFCN PZ254V-11-06P; LCSC C492405
J4: SSD1306 SPI OLED; PinHeader_1x07_P2.54mm_Vertical; MPN XFCN PZ254V-11-07P; LCSC C492406
J5: Protected 1S LiPo; JST_PH_S2B-PH-SM4-TB_1x02-1MP_P2.00mm_Horizontal; MPN JST S2B-PH-SM4-TB
JP1: 1-2 RUN / 2-3 CHARGE; PinHeader_1x03_P2.54mm_Vertical; MPN Samtec TSW-103-07-G-S + one shunt
R1, R2: 5.1k; R_0603_1608Metric; MPN 0603WAF5101T5E; LCSC C23186
R3, R4, R5, R9, R10, R11: 10k; R_0603_1608Metric; MPN 0603WAF1002T5E; LCSC C25804
R6, R7: 4.7k; R_0603_1608Metric; MPN 0603WAF4701T5E; LCSC C23162
R12: 10k 100mA charge; R_0603_1608Metric; MPN 0603WAF1002T5E
SW1: RESET; SW_Push_1P1T_XKB_TS-1187A; MPN XKB TS-1187A-B-A-B; LCSC C318884
SW2: BOOT; SW_Push_1P1T_XKB_TS-1187A; MPN XKB TS-1187A-B-A-B; LCSC C318884
U1: ESP32-WROOM-32E-N4; ESP32-WROOM-32E; MPN Espressif ESP32-WROOM-32E-N4; LCSC C701341
U2: AP2112K-3.3TRG1; SOT-23-5; MPN AP2112K-3.3TRG1; LCSC C51118
U3: SHT31-DIS-B; Sensirion_DFN-8-1EP_2.5x2.5mm_P0.5mm_EP1.1x1.7mm; MPN Sensirion SHT31-DIS-B2.5KS; LCSC C80862
U4: MCP73831T-2ACI/OT; SOT-23-5; MPN MCP73831T-2ACI/OT

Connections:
+3V3: C2.1, C3.1, C4.1, C6.1, C7.1, C8.1, J2.2, J3.2, J4.2, R3.1, R4.1, R5.1, R6.1, R7.1, R9.1, R10.1, U1.2 (VDD), U2.5 (VOUT), U3.5 (VDD)
+5V: C1.1, D1.1 (K), F1.2, U4.4 (V_{DD})
/BAT_PLUS: J5.1, JP1.2
/CC1: J1.A5 (CC1), R1.1
/CC2: J1.B5 (CC2), R2.1
/CHARGE_BAT: C9.1, JP1.3, U4.3 (V_{BAT})
/EN: C5.1, J3.5, R3.2, SW1.1, U1.3 (EN)
/I2C_SCL: J2.3, R7.2, U1.36 (IO22), U3.4 (SCL)
/I2C_SDA: J2.4, R6.2, U1.33 (IO21), U3.1 (SDA)
/IO0: J3.6, R4.2, SW2.1, U1.25 (IO0)
/OLED_CS: J4.7, R10.2, U1.12 (IO27)
/OLED_DC: J4.6, R11.1, U1.11 (IO26)
/OLED_RST: J4.5, R9.2, U1.10 (IO25)
/PROG: R12.1, U4.5 (PROG)
/SHT_NRST: R5.2, U3.6 (~RESET)
/SPI_MOSI: J4.4, U1.37 (IO23)
/SPI_SCLK: J4.3, U1.30 (IO18)
/SYS: C10.1, JP1.1, U2.1 (VIN), U2.3 (EN)
/U0RXD: J3.4, U1.34 (RXD0/IO3)
/U0TXD: J3.3, U1.35 (TXD0/IO1)
GND: C1.2, C2.2, C3.2, C4.2, C5.2, C6.2, C7.2, C8.2, C9.2, C10.2, D1.2 (A), J1.A1 (GND), J1.A12 (GND), J1.B1 (GND), J1.B12 (GND), J1.S1 (SHIELD), J2.1, J3.1, J4.1, J5.2, R1.2, R2.2, R11.2, R12.2, SW1.2, SW2.2, U1.1 (GND), U1.15 (GND), U1.38 (GND), U1.39 (GND), U2.2 (GND), U3.2 (ADDR), U3.7 (R), U3.8 (VSS), U3.9 (VSS), U4.2 (V_{SS})
VBUS: F1.1, J1.A4 (VBUS), J1.A9 (VBUS), J1.B4 (VBUS), J1.B9 (VBUS)

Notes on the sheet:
ESP32-WROOM-32E: EN RC reset (10k/1uF), GPIO0 BOOT strap; antenna overhang
UART0 programming header (3.3 V adapter only; do not back-feed 3V3 while USB is plugged in)
I2C @100 kHz: SHT31 0x44 on GPIO21/22; J2 expansion has 4.7k pull-ups
J4 SPI OLED: GND, 3V3, SCLK18, MOSI23, RESET25, DC26, CS27
Mounting holes (M3)
USB-C charges only; AP2112K 600mA 55uA IQ; no always-on power LED
JP1: ONE shunt only, 1-2 RUN or 2-3 CHARGE. Remove USB before moving shunt. Charge disconnects all node loads.
Protected 1S 4.2V LiPo >=500mAh, >=1A pulse. 100mA charge; no cell temperature supervision. Supervised room-temperature charging only.

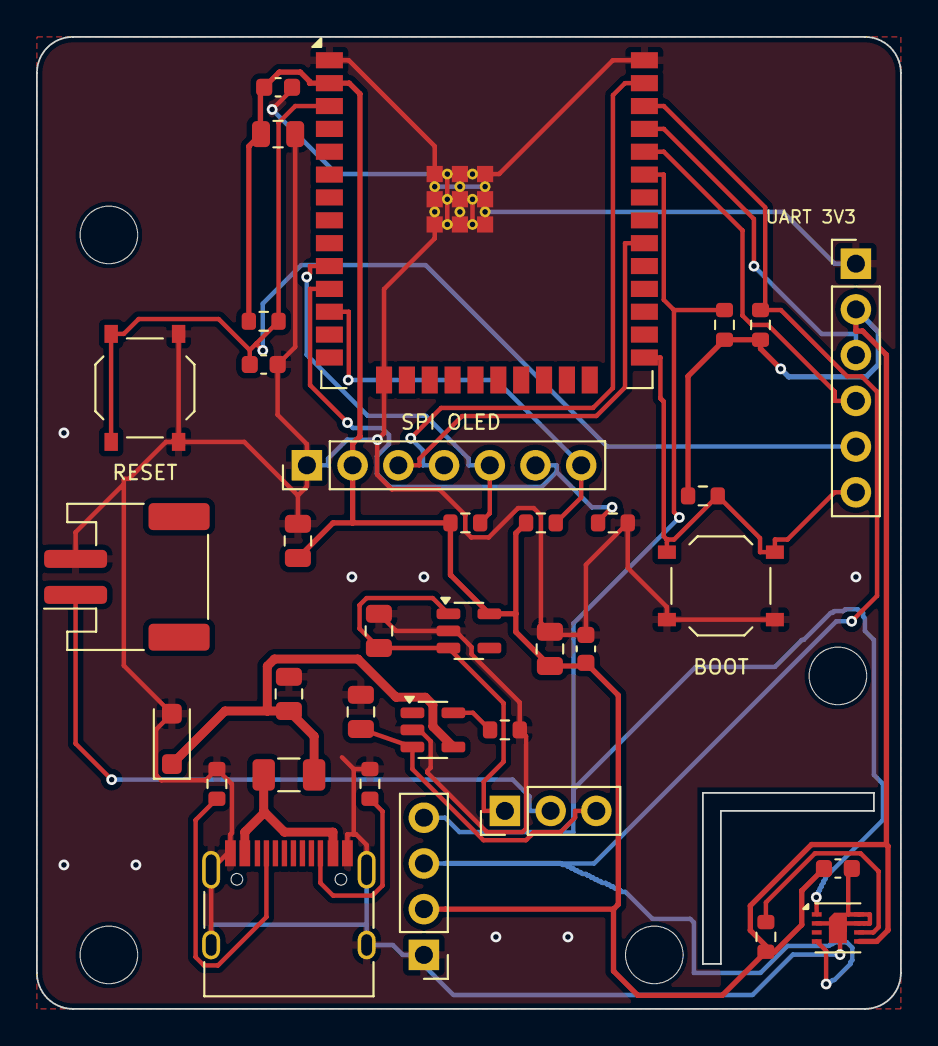
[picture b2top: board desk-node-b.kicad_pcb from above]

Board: 2 copper layers, 48.0 x 54.0 mm, 39 parts (0 on the bottom side), 22 nets.

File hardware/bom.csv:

"Designator","Value","Footprint","LCSC","MPN","Qty"
"C1,C7","10uF 25V","Capacitor_SMD:C_0805_2012Metric","C15850","CL21A106KAYNNNE","2"
"C2,C3","22uF 16V","Capacitor_SMD:C_0805_2012Metric","C98190","CL21A226MOQNNNE","2"
"C4,C6,C8","100nF","Capacitor_SMD:C_0603_1608Metric","C1591","CL10B104KB8NNNC","3"
"C5","1uF","Capacitor_SMD:C_0603_1608Metric","C15849","CL10A105KB8NNNC","1"
"D1","SMF5.0A","Diode_SMD:D_SOD-123F","C193402","MDD SMF5.0A (5 V TVS)","1"
"D2","Red","LED_SMD:LED_0603_1608Metric","C2286","KT-0603R","1"
"F1","750mA","Fuse:Fuse_1206_3216Metric","C99563","Littelfuse 1206L075THYR","1"
"J1","USB-C power","Connector_USB:USB_C_Receptacle_HRO_TYPE-C-31-M-12","C165948","HRO TYPE-C-31-M-12","1"
"J2","I2C expansion","Connector_PinHeader_2.54mm:PinHeader_1x04_P2.54mm_Vertical","C492403","XFCN PZ254V-11-04P","1"
"J3","UART0 prog","Connector_PinHeader_2.54mm:PinHeader_1x06_P2.54mm_Vertical","C492405","XFCN PZ254V-11-06P","1"
"J4","SSD1306 SPI OLED","Connector_PinHeader_2.54mm:PinHeader_1x07_P2.54mm_Vertical","C492406","XFCN PZ254V-11-07P","1"
"R1,R2","5.1k","Resistor_SMD:R_0603_1608Metric","C23186","0603WAF5101T5E","2"
"R3,R4,R5,R9,R10,R11","10k","Resistor_SMD:R_0603_1608Metric","C25804","0603WAF1002T5E","6"
"R6,R7","4.7k","Resistor_SMD:R_0603_1608Metric","C23162","0603WAF4701T5E","2"
"R8","1k","Resistor_SMD:R_0603_1608Metric","C21190","0603WAF1001T5E","1"
"SW1","RESET","Button_Switch_SMD:SW_Push_1P1T_XKB_TS-1187A","C318884","XKB TS-1187A-B-A-B","1"
"SW2","BOOT","Button_Switch_SMD:SW_Push_1P1T_XKB_TS-1187A","C318884","XKB TS-1187A-B-A-B","1"
"U1","ESP32-WROOM-32E-N4","DeskNode:ESP32-WROOM-32E","C701341","Espressif ESP32-WROOM-32E-N4","1"
"U2","AZ1117CH-3.3TRG1","Package_TO_SOT_SMD:SOT-223-3_TabPin2","C92102","AZ1117CH-3.3TRG1","1"
"U3","SHT31-DIS-B","Sensor_Humidity:Sensirion_DFN-8-1EP_2.5x2.5mm_P0.5mm_EP1.1x1.7mm","C80862","Sensirion SHT31-DIS-B2.5KS","1"
